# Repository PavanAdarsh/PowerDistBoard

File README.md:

A PCB designed for power distribution from a 16V battery to 6 T200 thrusters, using MOSFET switching action. A kill switch circuit is also implemented.

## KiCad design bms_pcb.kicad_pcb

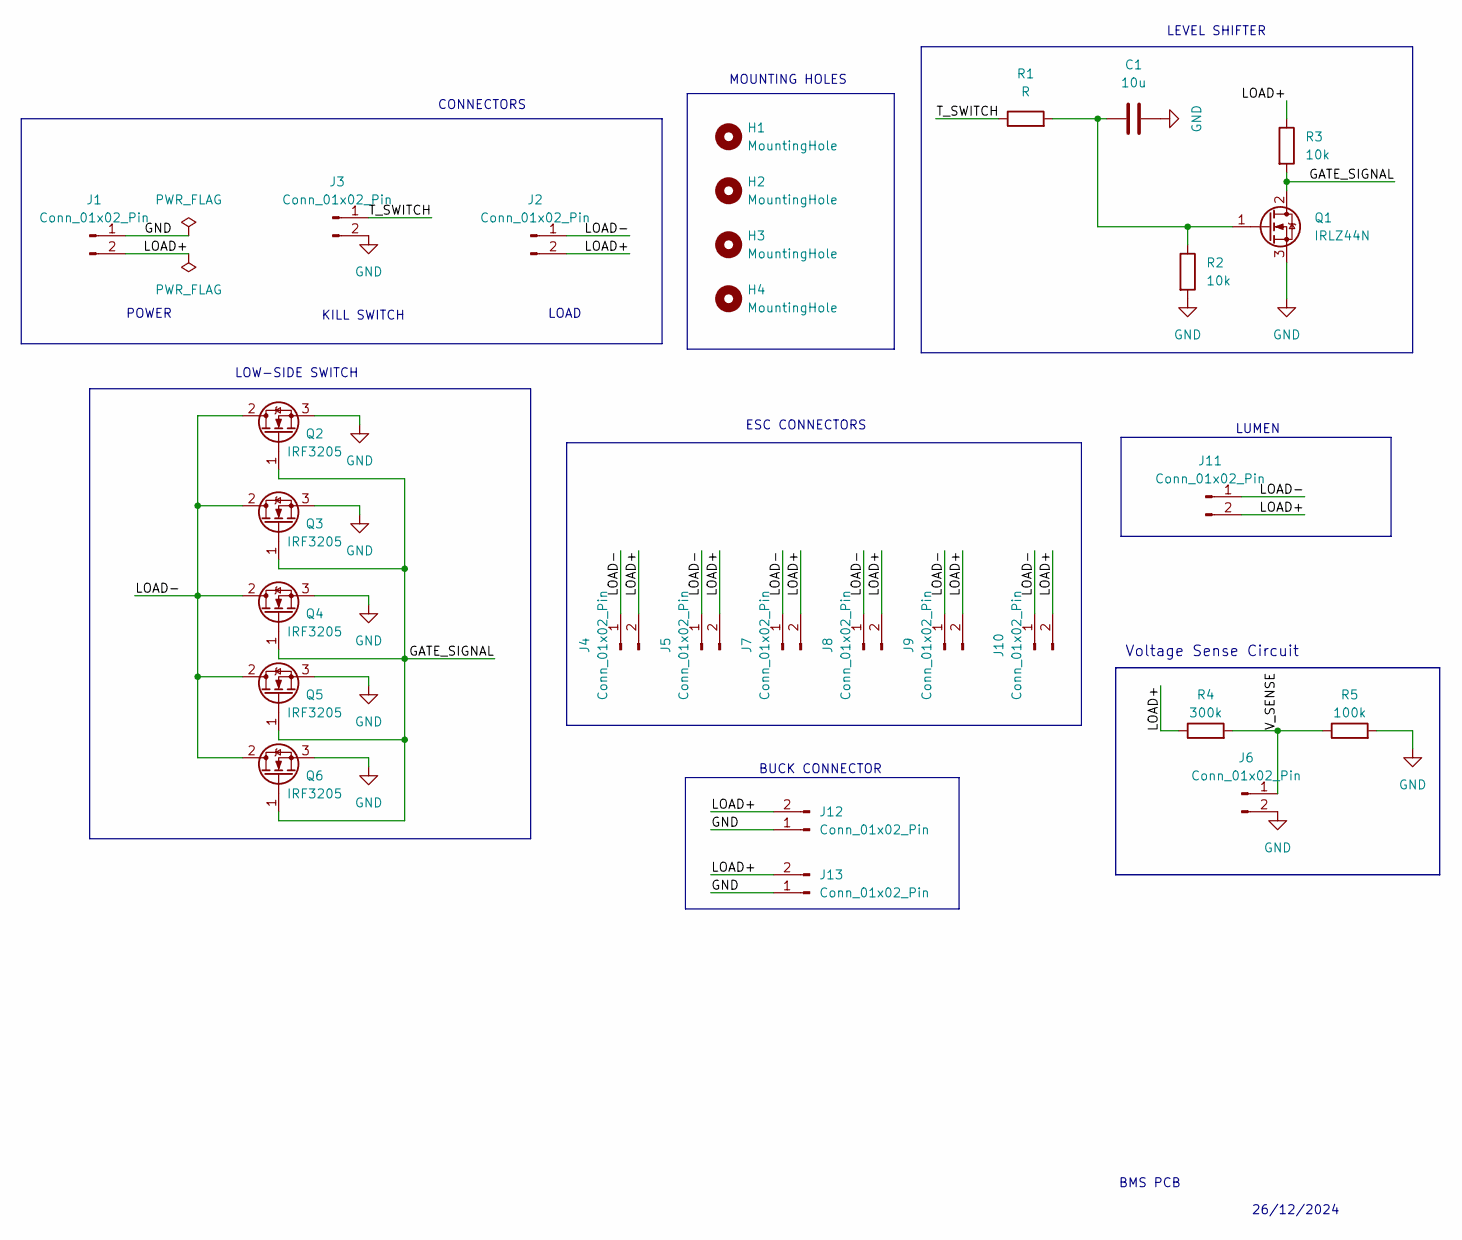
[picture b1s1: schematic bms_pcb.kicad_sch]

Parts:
C1: 10u; C_Disc_D3.0mm_W1.6mm_P2.50mm
H1, H2, H3, H4: MountingHole; MountingHole_3.2mm_M3
J1, J2, J4, J5, J7, J8, J9, J10, J11: Conn_01x02_Pin; xt-60_hole
J3, J6: Conn_01x02_Pin; JST_EH_B2B-EH-A_1x02_P2.50mm_Vertical
J12, J13: Conn_01x02_Pin; AMASS_XT30UPB-F_1x02_P5.0mm_Vertical
Q1: IRLZ44N; TO-220-3_Vertical
Q2, Q3, Q4, Q5, Q6: IRF3205; TO-220-3_Vertical
R1: R; resistor_holes
R2, R3: 10k; resistor_holes
R4: 300k; resistor_holes
R5: 100k; resistor_holes

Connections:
/GATE_SIGNAL: Q1.2 (D), Q2.1 (G), Q3.1 (G), Q4.1 (G), Q5.1 (G), Q6.1 (G), R3.2
/LOAD+: J1.2, J2.2, J4.2, J5.2, J7.2, J8.2, J9.2, J10.2, J11.2, J12.2, J13.2, R3.1, R4.1
/LOAD-: J2.1, J4.1, J5.1, J7.1, J8.1, J9.1, J10.1, J11.1, Q2.2 (D), Q3.2 (D), Q4.2 (D), Q5.2 (D), Q6.2 (D)
/T_SWITCH: J3.1, R1.1
/V_SENSE: J6.1, R4.2, R5.1
GND: C1.2, J1.1, J3.2, J6.2, J12.1, J13.1, Q1.3 (S), Q2.3 (S), Q3.3 (S), Q4.3 (S), Q5.3 (S), Q6.3 (S), R2.2, R5.2
unnamed: C1.1, Q1.1 (G), R1.2, R2.1

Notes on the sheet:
KILL SWITCH
ESC CONNECTORS
BMS PCB
BUCK CONNECTOR
LEVEL SHIFTER
LUMEN
MOUNTING HOLES
CONNECTORS
LOAD
LOW-SIDE SWITCH
26/12/2024
POWER
Voltage Sense Circuit

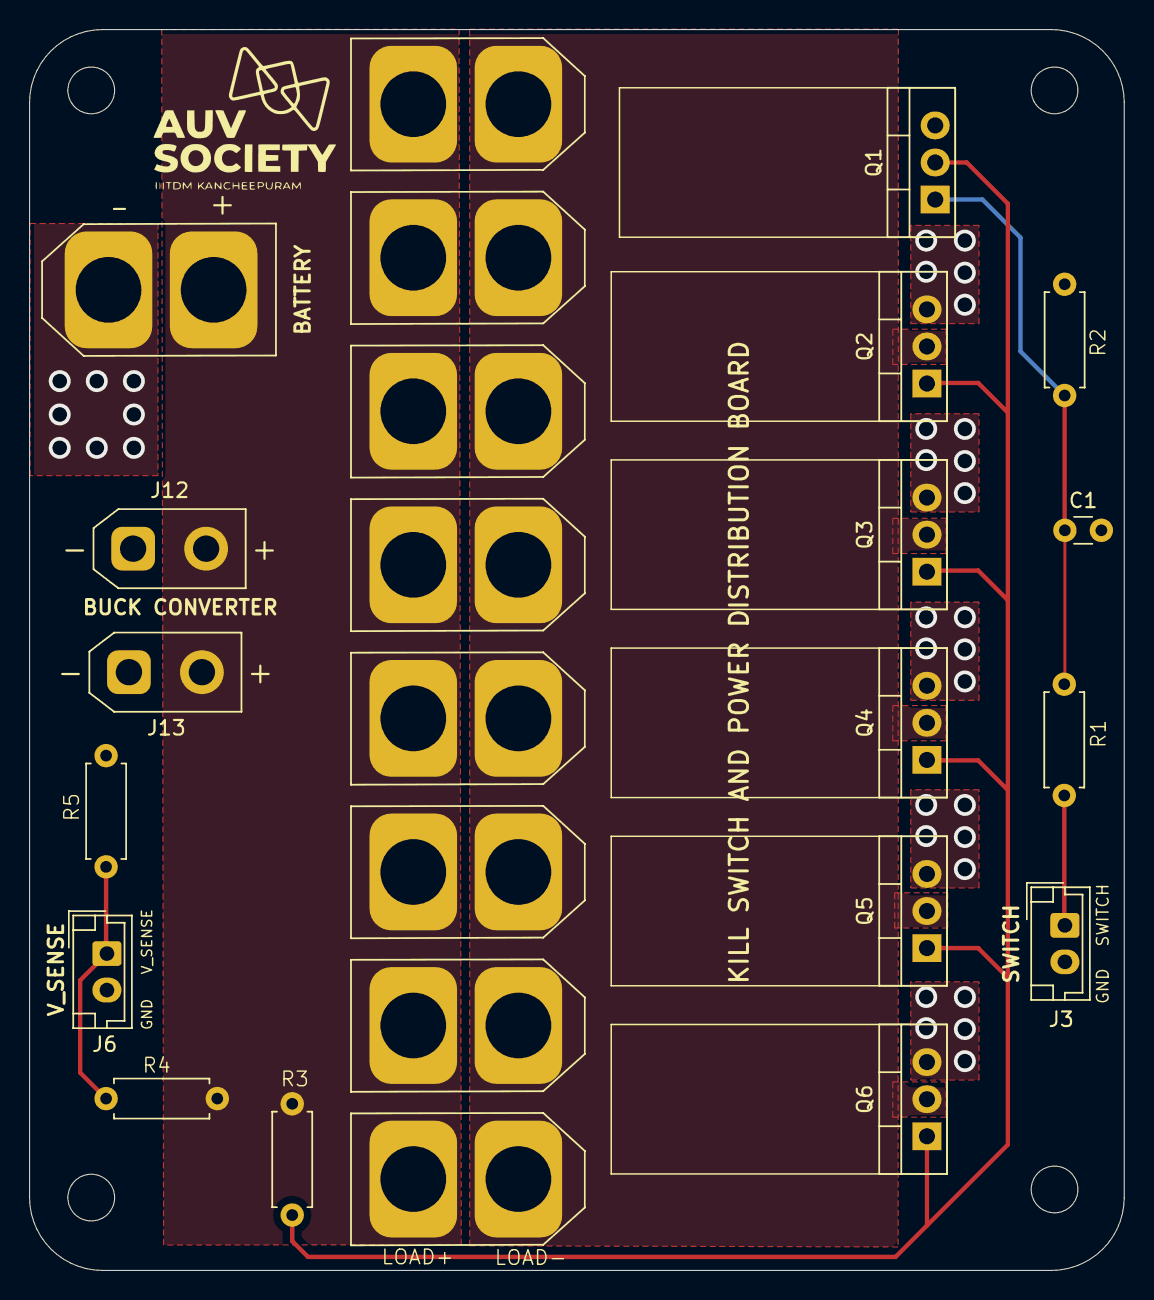
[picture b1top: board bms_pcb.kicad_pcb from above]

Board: 2 copper layers, 75.0 x 85.0 mm, 29 parts (0 on the bottom side), 7 nets.
